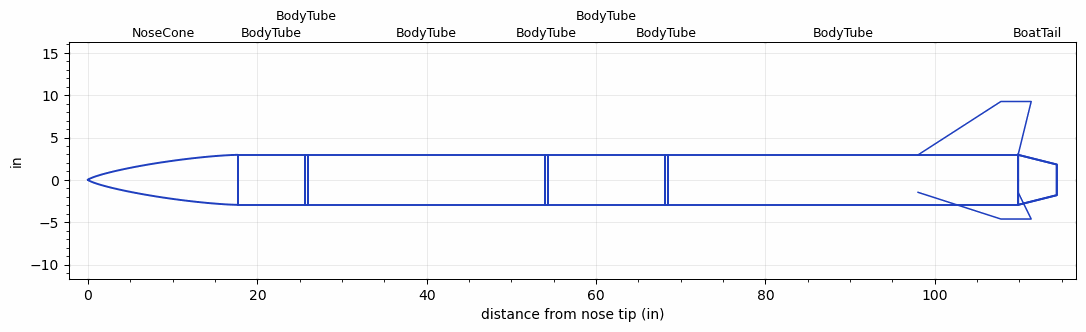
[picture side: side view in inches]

<RASAeroDocument>
 <FileVersion>2</FileVersion>
 <RocketDesign>
  <NoseCone>
   <Length>17.7165</Length>
   <Diameter>5.9055</Diameter>
   <Shape>Von Karman Ogive</Shape>
   <Location>0</Location>
  </NoseCone>
  <BodyTube>
   <Length>7.874</Length>
   <Diameter>5.9055</Diameter>
   <Location>17.7165</Location>
   <Protuberance>
    <StreamlinedNoBaseDrag>0</StreamlinedNoBaseDrag>
    <StreamlinedWithBaseDrag>0.121</StreamlinedWithBaseDrag>
    <InclinedPlate1Angle>0</InclinedPlate1Angle>
    <InclinedPlate1FrontalArea>0</InclinedPlate1FrontalArea>
    <InclinedPlate2Angle>0</InclinedPlate2Angle>
    <InclinedPlate2FrontalArea>0</InclinedPlate2FrontalArea>
   </Protuberance>
  </BodyTube>
  <BodyTube>
   <Length>0.3937</Length>
   <Diameter>5.9055</Diameter>
   <Location>25.5905</Location>
  </BodyTube>
  <BodyTube>
   <Length>27.9527</Length>
   <Diameter>5.9055</Diameter>
   <Location>25.9842</Location>
   <Protuberance>
    <StreamlinedNoBaseDrag>0</StreamlinedNoBaseDrag>
    <StreamlinedWithBaseDrag>0.404</StreamlinedWithBaseDrag>
    <InclinedPlate1Angle>0</InclinedPlate1Angle>
    <InclinedPlate1FrontalArea>0</InclinedPlate1FrontalArea>
    <InclinedPlate2Angle>0</InclinedPlate2Angle>
    <InclinedPlate2FrontalArea>0</InclinedPlate2FrontalArea>
   </Protuberance>
  </BodyTube>
  <BodyTube>
   <Length>0.3937</Length>
   <Diameter>5.9055</Diameter>
   <Location>53.9369</Location>
  </BodyTube>
  <BodyTube>
   <Length>13.7795</Length>
   <Diameter>5.9055</Diameter>
   <Location>54.3306</Location>
   <Protuberance>
    <StreamlinedNoBaseDrag>0</StreamlinedNoBaseDrag>
    <StreamlinedWithBaseDrag>0.246</StreamlinedWithBaseDrag>
    <InclinedPlate1Angle>0</InclinedPlate1Angle>
    <InclinedPlate1FrontalArea>0</InclinedPlate1FrontalArea>
    <InclinedPlate2Angle>0</InclinedPlate2Angle>
    <InclinedPlate2FrontalArea>0</InclinedPlate2FrontalArea>
   </Protuberance>
  </BodyTube>
  <BodyTube>
   <Length>0.3937</Length>
   <Diameter>5.9055</Diameter>
   <Location>68.1101</Location>
  </BodyTube>
  <BodyTube>
   <Length>41.3385</Length>
   <Diameter>5.9055</Diameter>
   <RailGuideDiameter>0.63</RailGuideDiameter>
   <RailGuideHeight>0.55</RailGuideHeight>
   <Location>68.5038</Location>
   <BoattailLength>4.5669</BoattailLength>
   <BoattailRearDiameter>3.622</BoattailRearDiameter>
   <Fin>
    <Count>3</Count>
    <Chord>11.811</Chord>
    <Span>6.2992</Span>
    <SweepDistance>9.7744</SweepDistance>
    <TipChord>3.5827</TipChord>
    <Thickness>0.2992</Thickness>
    <Location>11.811</Location>
    <AirfoilSection>Hexagonal Blunt Base</AirfoilSection>
    <FX1>0.3</FX1>
   </Fin>
   <Protuberance>
    <StreamlinedNoBaseDrag>0</StreamlinedNoBaseDrag>
    <StreamlinedWithBaseDrag>0.6</StreamlinedWithBaseDrag>
    <InclinedPlate1Angle>0</InclinedPlate1Angle>
    <InclinedPlate1FrontalArea>0</InclinedPlate1FrontalArea>
    <InclinedPlate2Angle>0</InclinedPlate2Angle>
    <InclinedPlate2FrontalArea>0</InclinedPlate2FrontalArea>
   </Protuberance>
  </BodyTube>
  <BoatTail>
   <Length>4.5669</Length>
   <Diameter>5.9055</Diameter>
   <RearDiameter>3.622</RearDiameter>
   <Location>109.8423</Location>
  </BoatTail>
  <Surface>Camouflage Paint</Surface>
  <ModifiedBarrowman>False</ModifiedBarrowman>
  <Turbulence>False</Turbulence>
  <UseBooster1>False</UseBooster1>
  <UseBooster2>False</UseBooster2>
 </RocketDesign>
 <LaunchSite>
  <Altitude>95.1444</Altitude>
  <Pressure>29.8209</Pressure>
  <RodAngle>5</RodAngle>
  <RodLength>39.3701</RodLength>
  <Temperature>58.6607</Temperature>
  <WindSpeed>4.4739</WindSpeed>
 </LaunchSite>
 <Recovery>
  <Altitude1>0</Altitude1>
  <Altitude2>0</Altitude2>
  <DeviceType1>None</DeviceType1>
  <DeviceType2>None</DeviceType2>
  <Event1>False</Event1>
  <Event2>False</Event2>
  <Size1>0</Size1>
  <Size2>0</Size2>
  <EventType1>None</EventType1>
  <EventType2>None</EventType2>
  <CD1>0</CD1>
  <CD2>0</CD2>
 </Recovery>
 <SimulationList>
  <Simulation>
   <SustainerLaunchWt>60.2141</SustainerLaunchWt>
   <SustainerCG>69.7315</SustainerCG>
   <SustainerIgnitionDelay>0</SustainerIgnitionDelay>
   <Booster1SeparationDelay>0</Booster1SeparationDelay>
   <Booster1IgnitionDelay>0</Booster1IgnitionDelay>
   <IncludeBooster1>False</IncludeBooster1>
   <Booster2Delay>0</Booster2Delay>
   <IncludeBooster2>False</IncludeBooster2>
  </Simulation>
 </SimulationList>
</RASAeroDocument>
